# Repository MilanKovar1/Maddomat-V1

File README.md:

# Maddomat-V1
Combustion boiler control

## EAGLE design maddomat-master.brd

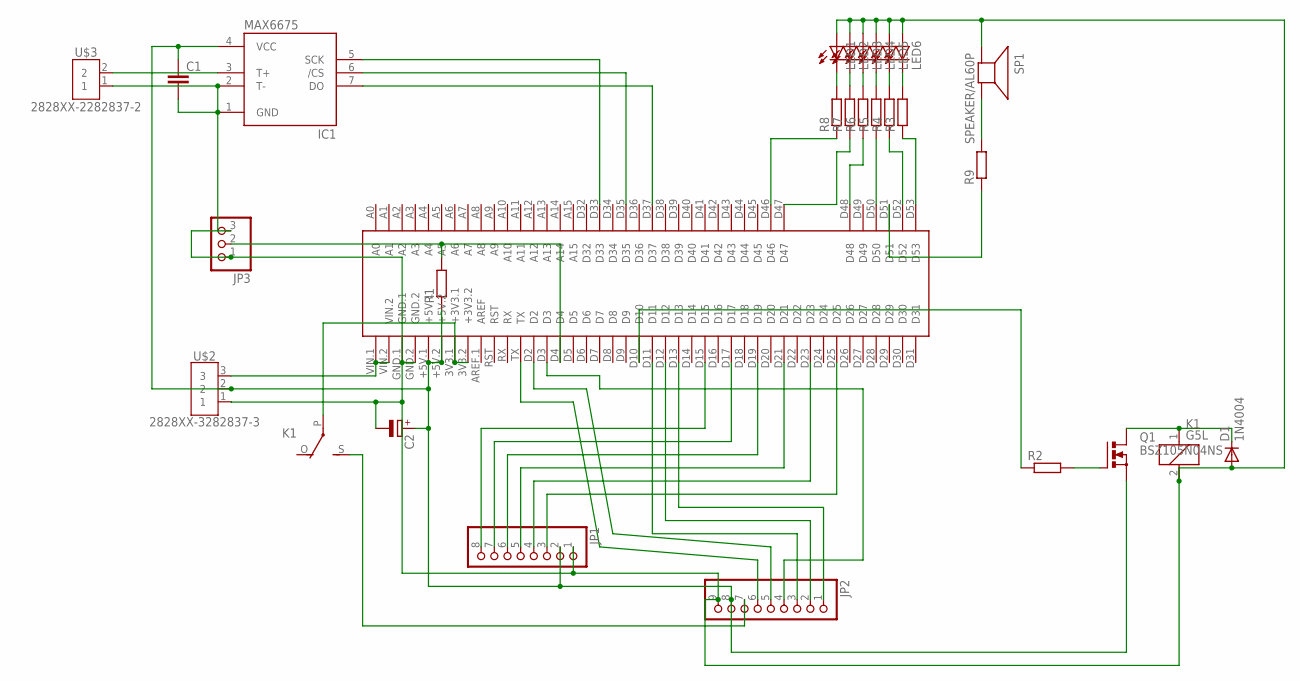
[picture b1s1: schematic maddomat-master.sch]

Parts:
C1: C-EUC0805; C0805
C2: CPOL-EUE5-10.5; E5-10,5
D1: 1N4004; DO41-10
IC1: MAX6675; SO08
JP1: PINHD-1X8; 1X08
JP2: PINHD-1X9; 1X09
JP3: PINHD-1X3; 1X03
K1: G5L; G5LE
LED1, LED2, LED3, LED4, LED5, LED6: LEDCHIP-LED0805; CHIP-LED0805
Q1: BSZ105N04NS; PG-TDSON-8
R1, R2, R3, R4, R5, R6, R7, R8, R9: R-EU_M0805; M0805
SP1: SPEAKER/AL60P; AL60P
U$1: MEGA2560_MIKRO
U$2: 2828XX-3282837-3; TERMBLK_508-3N
U$3: 2828XX-2282837-2; TERMBLK_508-2N

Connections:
unnamed: U$1.VIN.1, U$1.VIN.2, U$2.3
unnamed: R2.1, U$1.D10
unnamed: C1.1, C2.+, IC1.4 (VCC), JP1.2, JP2.8, Q1.1 (S), Q1.2 (S), Q1.3 (S), R1.1, U$1.+5V.1, U$1.+5V.2, U$2.2
unnamed: K1.P, U$1.3V3.1 (+3V3.1), U$1.3V3.2 (+3V3.2)
unnamed: JP1.8, U$1.D15
unnamed: JP1.7, U$1.D17
unnamed: JP1.6, U$1.D19
unnamed: JP2.1, U$1.D13
unnamed: JP1.5, U$1.D21
unnamed: JP1.4, U$1.D23
unnamed: JP1.3, U$1.D25
unnamed: JP2.2, U$1.D12
unnamed: JP2.3, U$1.D11
unnamed: JP2.6, U$1.TX
unnamed: JP2.5, U$1.D2
unnamed: JP2.4, U$1.D3
unnamed: JP2.7, K1.S
unnamed: D1.C, K1.1, Q1.5 (D), Q1.6 (D), Q1.7 (D), Q1.8 (D), Q1.TH (D)
unnamed: Q1.4 (G), R2.2
unnamed: JP3.2, R1.2, U$1.D4
unnamed: C1.2, C2.-, D1.A, IC1.1 (GND), IC1.2 (T-), JP1.1, JP2.9, JP3.1, JP3.3, K1.2, LED1.A, LED2.A, LED3.A, LED4.A, LED5.A, LED6.A, SP1.1 (+), U$1.GND.1, U$1.GND.2, U$2.1, U$3.1
unnamed: R3.1, U$1.D53
unnamed: R4.1, U$1.D52
unnamed: R5.1, U$1.D50
unnamed: R6.1, U$1.D48
unnamed: R7.1, U$1.D47
unnamed: R8.1, U$1.D46
unnamed: LED1.C, R8.2
unnamed: LED2.C, R7.2
unnamed: LED3.C, R6.2
unnamed: LED4.C, R5.2
unnamed: LED5.C, R4.2
unnamed: LED6.C, R3.2
unnamed: IC1.3 (T+), U$3.2
unnamed: IC1.5 (SCK), U$1.D33
unnamed: IC1.6 (/CS), U$1.D35
unnamed: IC1.7 (DO), U$1.D37
unnamed: R9.1, U$1.D51
unnamed: R9.2, SP1.2 (-)

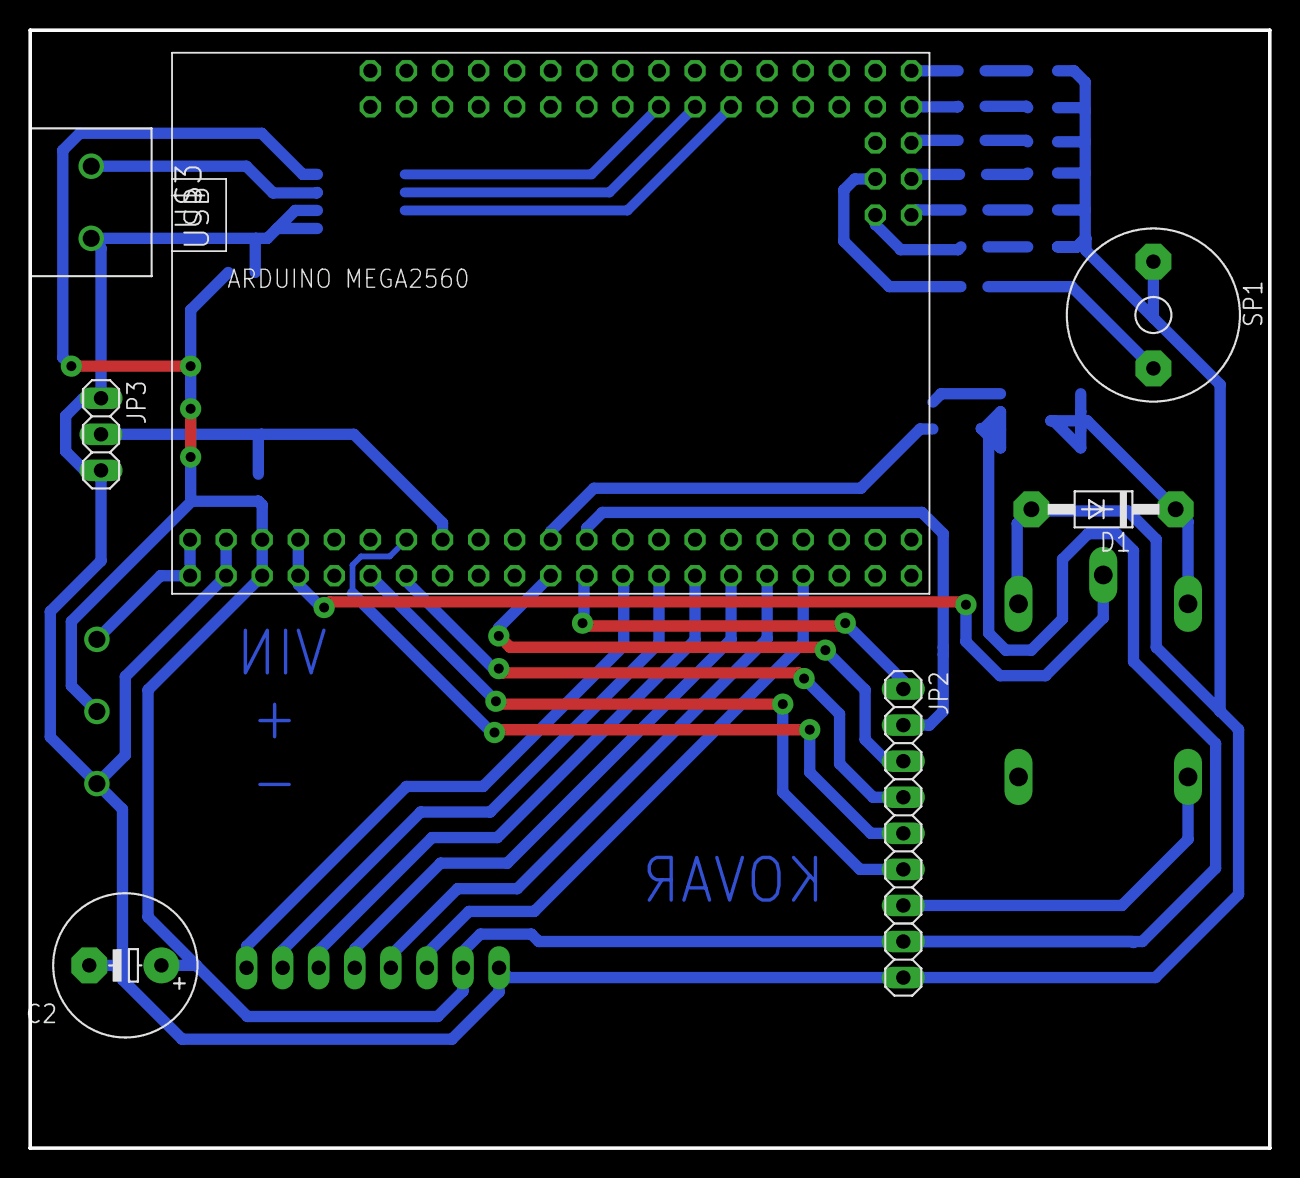
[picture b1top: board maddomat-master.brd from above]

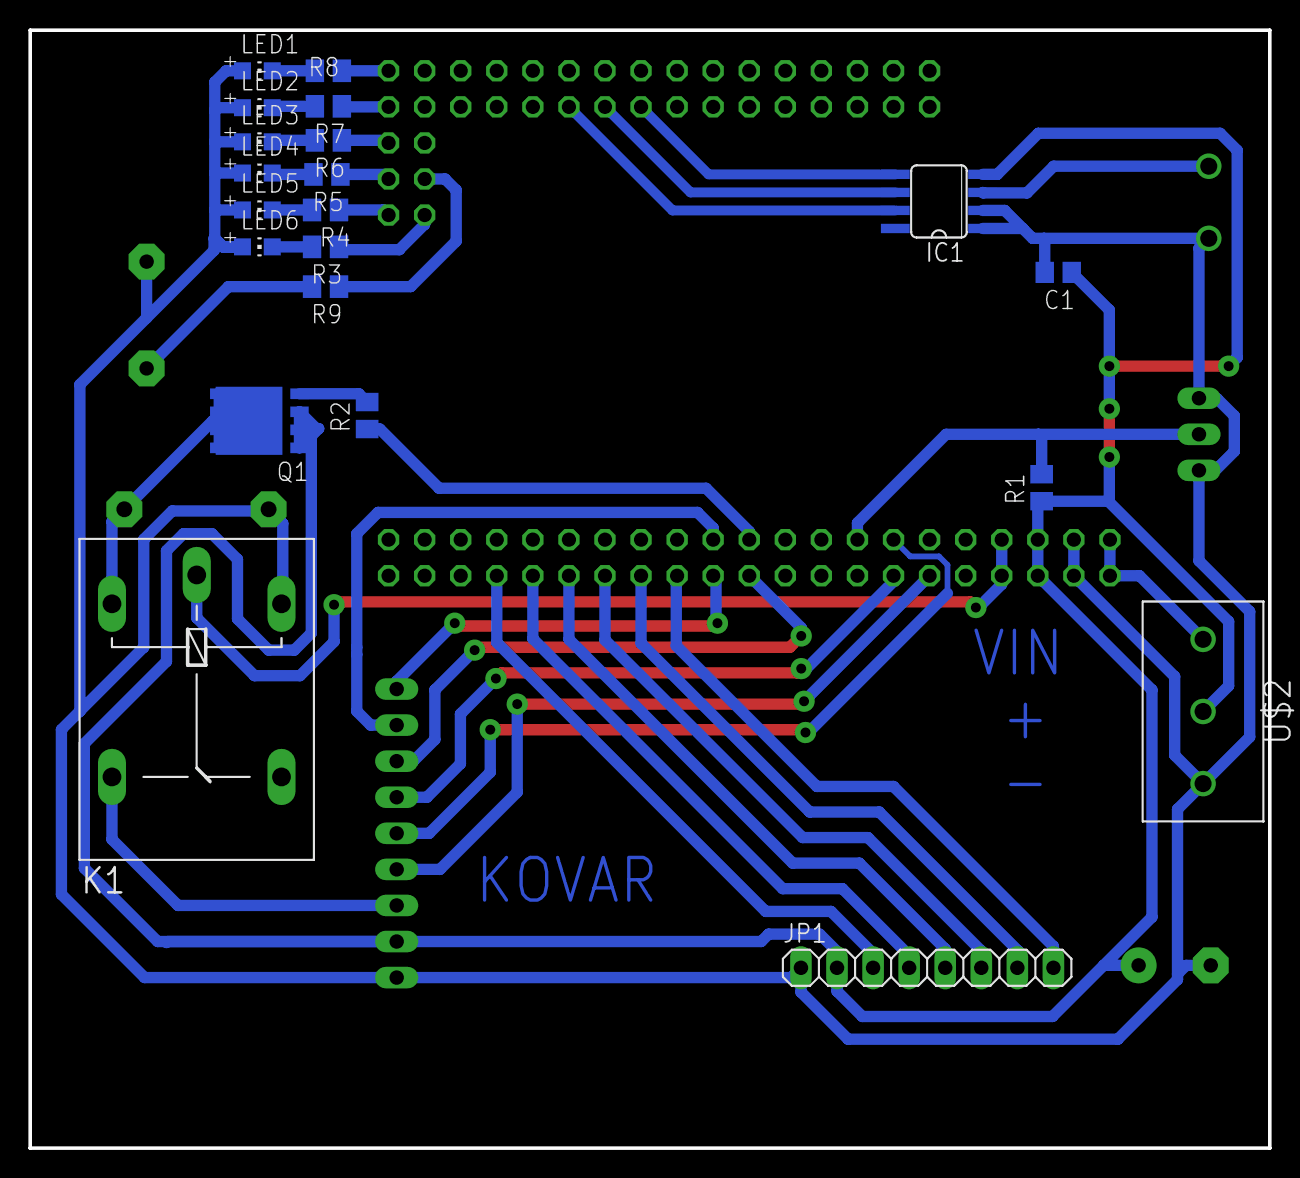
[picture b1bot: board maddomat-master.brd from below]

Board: 2 copper layers, 87.3 x 78.7 mm, 28 parts (21 on the bottom side), 39 nets.

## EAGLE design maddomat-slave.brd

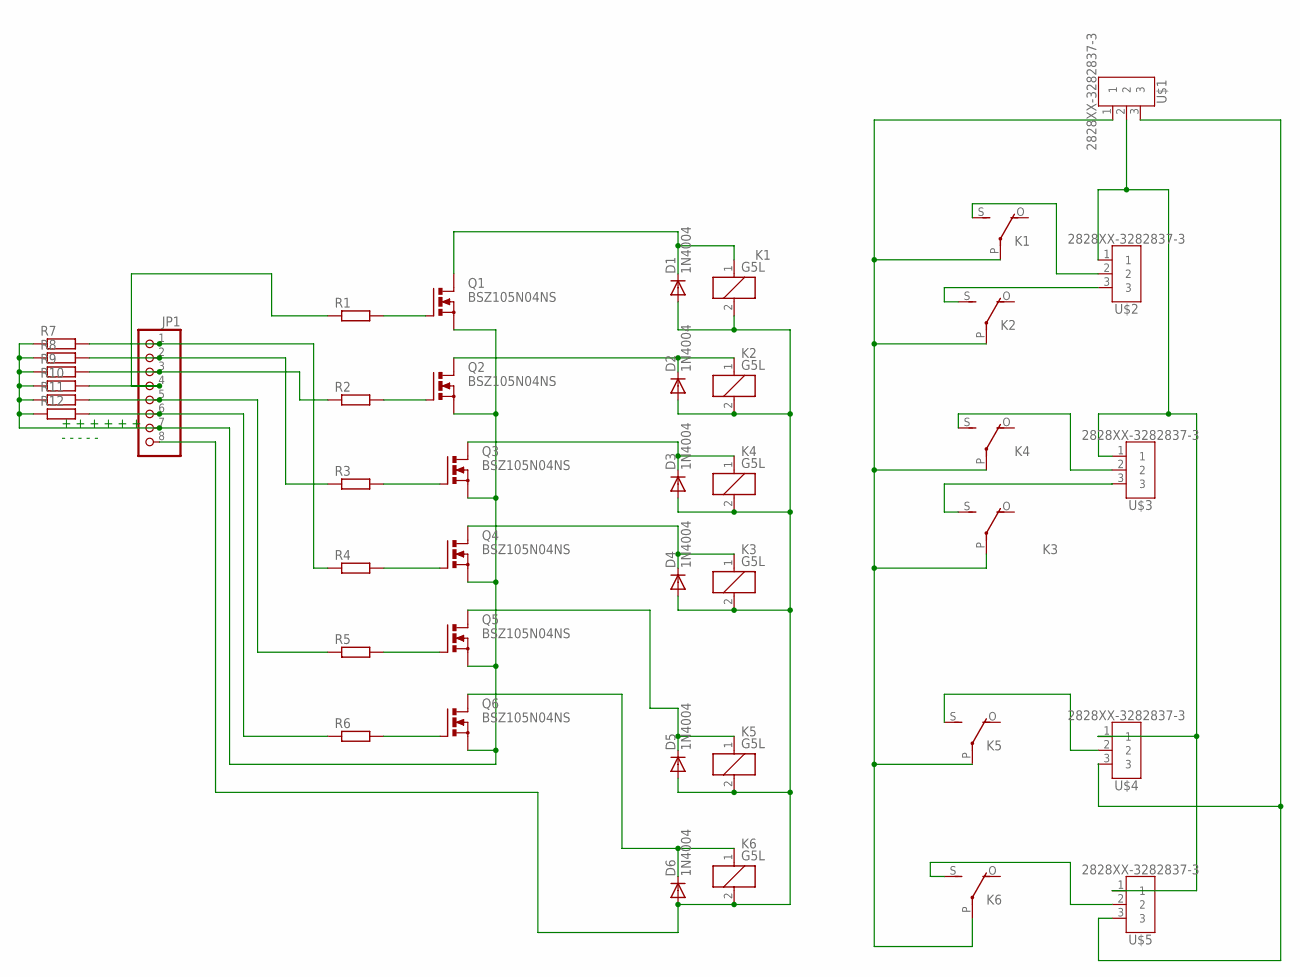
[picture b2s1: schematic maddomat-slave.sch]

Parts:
D1, D2, D3, D4, D5, D6: 1N4004; DO41-10
JP1: PINHD-1X8; 1X08
K1, K2, K3, K4, K5, K6: G5L; G5LE
Q1, Q2, Q3, Q4, Q5, Q6: BSZ105N04NS; PG-TDSON-8
R1, R2, R3, R4, R5, R6, R7, R8, R9, R10, R11, R12: R-EU_M0805; M0805
U$1, U$2, U$3, U$4, U$5: 2828XX-3282837-3; TERMBLK_508-3N

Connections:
unnamed: K1.S, U$2.2
unnamed: K2.S, U$2.3
unnamed: U$1.2, U$2.1, U$3.1, U$4.1, U$5.1
unnamed: K4.S, U$3.2
unnamed: K3.S, U$3.3
unnamed: K5.S, U$4.2
unnamed: K6.S, U$5.2
unnamed: K1.P, K2.P, K3.P, K4.P, K5.P, K6.P, U$1.1
unnamed: Q2.5 (D), Q2.6 (D), Q2.7 (D), Q2.8 (D), Q2.TH (D), Q3.5 (D), Q3.6 (D), Q3.7 (D), Q3.8 (D), Q3.TH (D)
unnamed: U$1.3, U$4.3, U$5.3
unnamed: D1.C, K1.1, Q1.5 (D), Q1.6 (D), Q1.7 (D), Q1.8 (D), Q1.TH (D)
unnamed: JP1.4, R1.1, R10.2
unnamed: JP1.3, R2.1, R9.2
unnamed: JP1.2, R3.1, R8.2
unnamed: JP1.1, R4.1, R7.2
unnamed: JP1.5, R5.1, R11.2
unnamed: JP1.6, R6.1, R12.2
unnamed: Q1.4 (G), R1.2
unnamed: Q2.4 (G), R2.2
unnamed: Q3.4 (G), R3.2
unnamed: Q4.4 (G), R4.2
unnamed: Q5.4 (G), R5.2
unnamed: Q6.4 (G), R6.2
unnamed: JP1.7, Q1.1 (S), Q1.2 (S), Q1.3 (S), Q2.1 (S), Q2.2 (S), Q2.3 (S), Q3.1 (S), Q3.2 (S), Q3.3 (S), Q4.1 (S), Q4.2 (S), Q4.3 (S), Q5.1 (S), Q5.2 (S), Q5.3 (S), Q6.1 (S), Q6.2 (S), Q6.3 (S), R7.1, R8.1, R9.1, R10.1, R11.1, R12.1
unnamed: D2.C, K2.1, Q2.5 (D), Q2.6 (D), Q2.7 (D), Q2.8 (D), Q2.TH (D)
unnamed: D3.C, K4.1, Q3.5 (D), Q3.6 (D), Q3.7 (D), Q3.8 (D), Q3.TH (D)
unnamed: D4.C, K3.1, Q4.5 (D), Q4.6 (D), Q4.7 (D), Q4.8 (D), Q4.TH (D)
unnamed: D5.C, K5.1, Q5.5 (D), Q5.6 (D), Q5.7 (D), Q5.8 (D), Q5.TH (D)
unnamed: D6.C, K6.1, Q6.5 (D), Q6.6 (D), Q6.7 (D), Q6.8 (D), Q6.TH (D)
unnamed: D1.A, D2.A, D3.A, D4.A, D5.A, D6.A, JP1.8, K1.2, K2.2, K3.2, K4.2, K5.2, K6.2

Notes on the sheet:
+ + + + + +
- - - - -

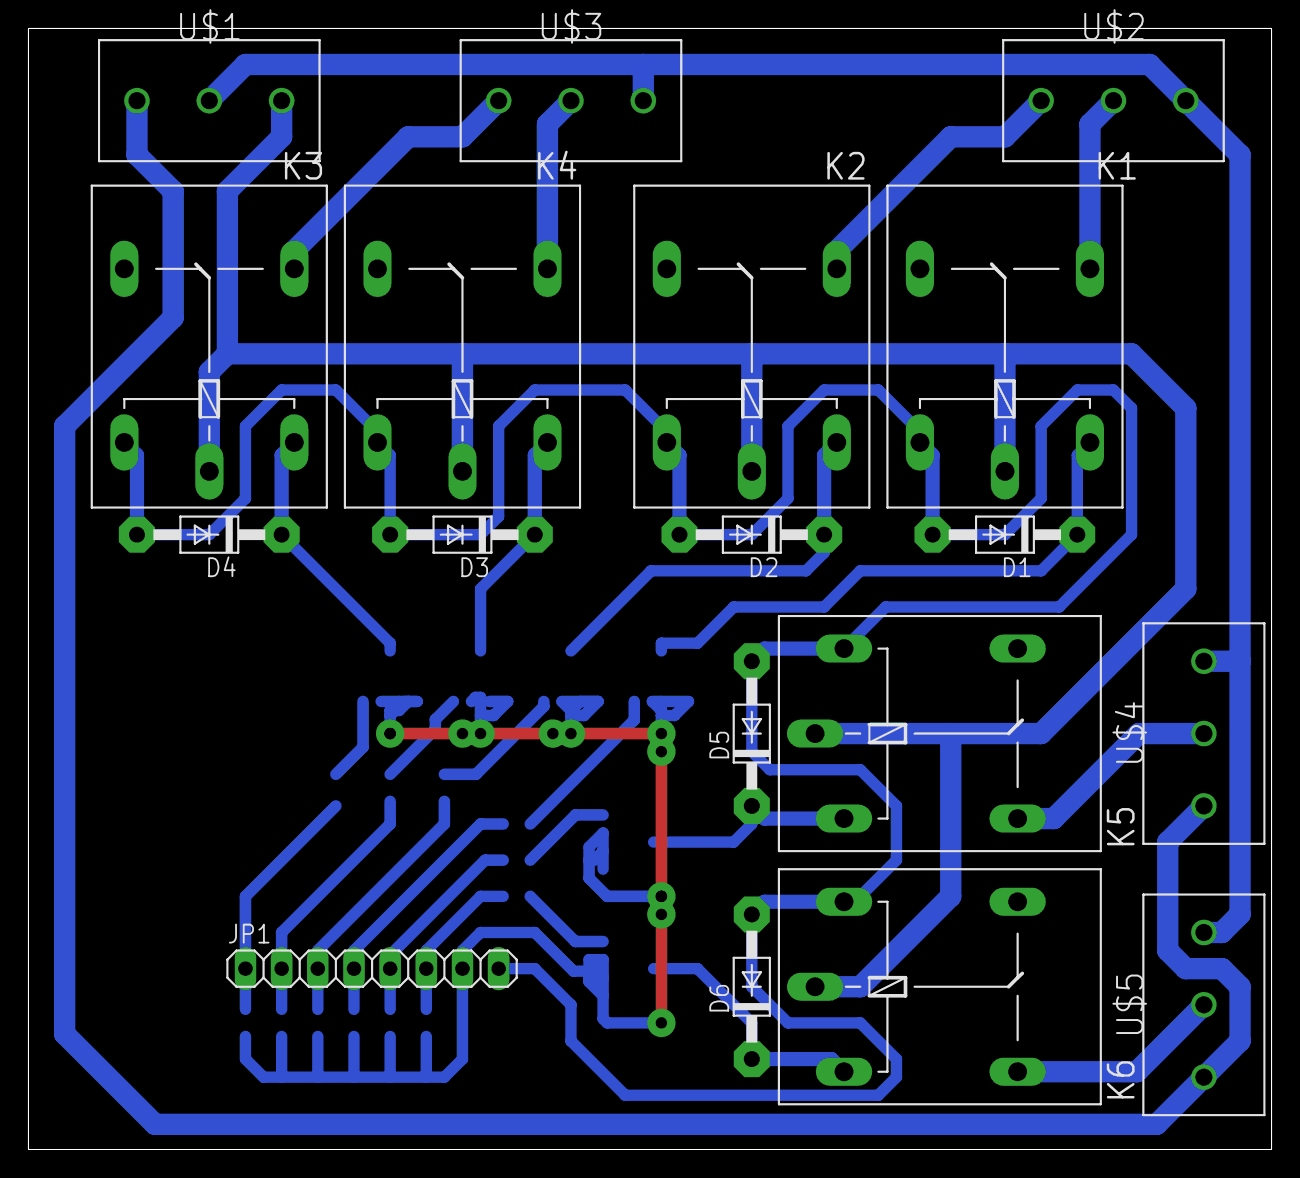
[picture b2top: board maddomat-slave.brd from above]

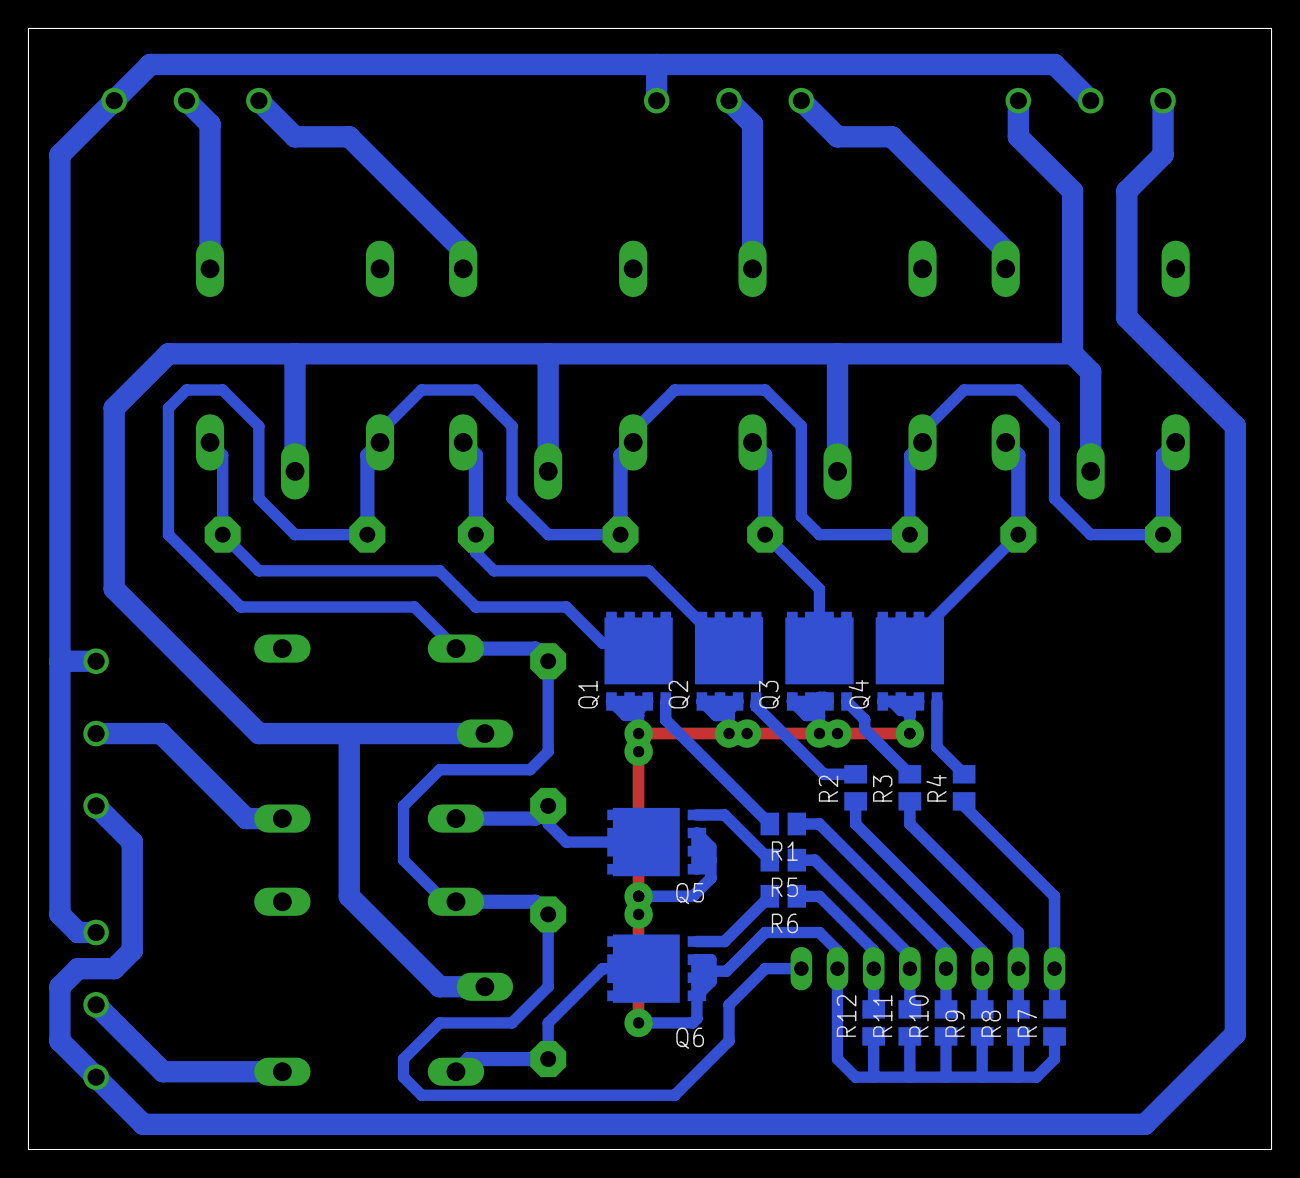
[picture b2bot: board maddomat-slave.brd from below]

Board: 2 copper layers, 87.3 x 78.7 mm, 36 parts (18 on the bottom side), 30 nets.

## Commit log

2022-01-07 Create Photos
